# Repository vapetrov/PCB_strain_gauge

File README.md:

# PCB Strain Gauge

A strain gauge, with amplifier, where the sensing element is the circuit board itself. Sensitive enough to measure deflections in the range of micrometers while having a full scale deflection range of +/- 3cm.

https://github.com/vapetrov/PCB_strain_gauge/assets/7529600/8c5e6594-8a19-4efe-8d25-b016dfba4ef4

### [View files with KiCanvas!](https://kicanvas.org/?github=https%3A%2F%2Fgithub.com%2Fvapetrov%2FPCB_strain_gauge)

## Manufacturing
The recommended board thickness is 0.6mm, although it could be made thicker or thinner for different applications. Thinner boards will result in a smaller output voltage swing.

- strain_gauge_3.zip
    - 20 mm x 118 mm, 2 layer
    - 0.15mm (~6mil) min trace width
    - 4-element sensing bridge
- strain_gauge_3_rotated.zip
    - Same as the previous one, except it uses 2-element sensing.
    - Lower thermal drift and bias from manufacturing (theoretically)
- stran_gauge_stiffener.zip
    - 20 mm x 42 mm rectangle to keep the component side from flexing
    - Can be affixed to the board with 3M VHB 5906

## Assembly
This project was made with hand-assembly in mind, and does not require hot air or a reflow oven.

The board can be used standalone with an integrated microcontroller (Seeed Studio XIAO RP2040) or an external microcontroller through the header pins.  
The external ADC (U5) can be omitted, and the analog voltage can be sampled directly on the "OUT" pin.  
The bias voltage generator (U8, U4) can also be omitted by placing a jumper wire between pins 2&3 on U8. Doing this will result in a measureable voltage on the output when no force is applied. 

## Programming

The included sample firmware will wait until a serial console is opened, perform a 5 second offset calibration, then sample continuously at the lowest gain setting. The `graph.py` script can be used to display the output.  
For high sensitivity measurements, it's important to let the board reach a stable operating temperature for at least 5 minutes before calibrating.

## Customatization

To customize the shape of the sensing element, `draw_footprint.ipynb` can be used to generate an outline of a given width, height and curvature. The resulting `.svg` can be imported into Inkscape and converted into a KiCad footprint using the [svg2shenzen](https://github.com/badgeek/svg2shenzhen) tool.

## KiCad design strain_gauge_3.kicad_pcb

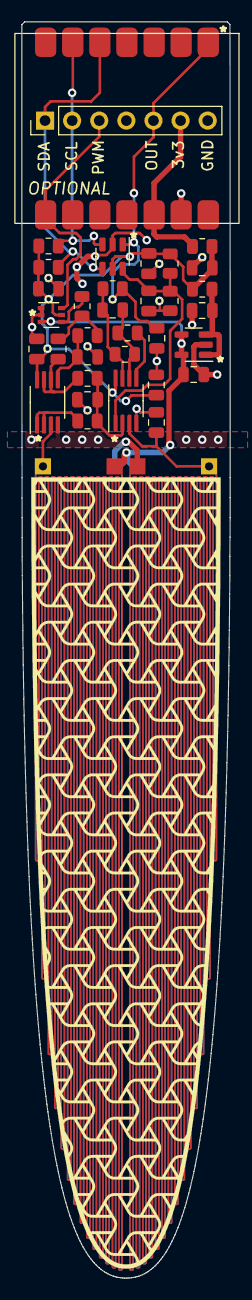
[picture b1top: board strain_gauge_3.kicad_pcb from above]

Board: 2 copper layers, 19.5 x 117.7 mm, 37 parts (0 on the bottom side), 21 nets.

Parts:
C1, C2, C5, C9, C10, C11, C12: 10u; C_0805_2012Metric
C3, C7, C13, C14: 47n; C_0805_2012Metric
C4, C6, C8: 100n; C_0805_2012Metric
FB1: FerriteBead_Small; R_0805_2012Metric
J1: Breakout Pins; PinHeader_1x07_P2.54mm_Vertical
R1: 12; R_0805_2012Metric
R2: 105k; R_0805_2012Metric
R3: 215k; R_0805_2012Metric
R5: 22k; R_0805_2012Metric
R6: 24; R_0805_2012Metric
R7, R8, R10, R11: 10k; R_0805_2012Metric
R9: 120; R_0805_2012Metric
R13: 1k; R_0805_2012Metric
R14: 12k; R_0805_2012Metric
Ref**: Val**; texture
U1: TLV75801PDBV; SOT-23-5
U2: MAX4208; MSOP-8_3x3mm_P0.65mm
U4: FSA5157P6X; SOT-363_SC-70-6
U5: MCP3425A0T-E/CH; SOT-23-6
U6: MOUDLE-SEEEDUINO-XIAO; MOUDLE14P-SMD-2.54-21X17.8MM
U7: bridge
U8: MCP6V67EMS; MSOP-8_3x3mm_P0.65mm
e: slot

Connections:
+3V3: C5.1, C9.1, C10.1, C11.1, C12.1, FB1.2, R1.1, R7.2, R10.2, R11.2, U2.8 (V+), U4.5 (Vcc), U5.5 (Vdd), U8.8 (V+)
/AMP_OUT: C8.2, J1.5, R9.2, U5.1 (VIN+), U6.1 (PA02_A0_D0)
/BRIDGE_BIAS: C4.2, R14.1, U8.6 (-), U8.7
/BRIDGE_SUPPLY: C2.1, U1.4 (FB), U1.5 (OUT), U4.3 (B0), U7.1
/PWM_BIAS: J1.3, U4.6 (Select), U6.8 (PB09_A7_D7_RX)
/REFIN: C7.2, R7.1, R8.2, U2.1 (REFIN), U5.6 (VIN-)
/SCL: J1.2, R10.1, U5.3 (SCL), U6.6 (PA9_A5_D5_SCL)
/SDA: J1.1, R11.1, U5.4 (SDA), U6.5 (PA8_A4_D4_SDA)
/VIN: FB1.1, J1.6, U6.12 (3V3)
GND: C1.2, C2.2, C3.2, C5.2, C7.1, C8.1, C9.2, C10.2, C11.2, C12.2, C13.1, C14.1, J1.7, R8.1, U1.2 (GND), U2.4 (V-), U4.1 (B1), U4.2 (GND), U5.2 (Vss), U6.13 (GND), U7.2, U8.4 (V-)
unnamed: C4.1, R2.2, R3.1
unnamed: C6.1, R5.1, R9.1, U2.7
unnamed: C1.1, R1.2, U1.1 (IN), U1.3 (EN)
unnamed: C13.2, U2.3 (+), U7.3 (+)
unnamed: C14.2, R13.2, R14.2, U2.2 (-)
unnamed: C6.2, R5.2, R6.1, U2.6 (FB)
unnamed: R6.2, U2.5 (REF)
unnamed: R2.1, U4.4 (COM)
unnamed: U7.4 (-), U8.3 (+)
unnamed: R13.1, U8.1, U8.2 (-)
unnamed: C3.1, R3.2, U8.5 (+)

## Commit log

2024-02-04 initial commit.
2024-02-05 gitignore
2024-02-05 removed files
2024-02-05 readme
2024-02-15 added schematic pdf
2024-06-04 Update draw_footprint.ipynb
    Made the right side mirror the left side instead of going horizontal.
    No idea if this was meant to be horizontal or not. Use it if you want or else disregard this commit.
2024-06-05 added variable to control right side rotation
